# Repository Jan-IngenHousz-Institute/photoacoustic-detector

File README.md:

# photoacoustic-detector

A photoacoustic detector built from a TLV320ADC6120 audio-ADC shield on a
Raspberry Pi Pico (RP2040), an IM73A135 MEMS microphone and an on/off
current source driving a LED. The Pico
switches the LED with a square wave between 200 Hz and 10 kHz, computes the
lock-in amplitude and phase of the microphone signal at that frequency and
streams the raw samples; the PC shows the FFT, the lock-in result and
frequency sweeps.

```
firmware/      Pico SDK (C) firmware, prebuilt image in firmware/release/
pc-gui/        desktop GUI (PySide6) and command-line tools
measurements/  recorded data (first recording 2026-10-30)
kicad/         shield schematic and PCB
doc/           datasheets (ADC, microphone, TI analog-input app note)
legacy/        superseded MicroPython firmware, reference only
```

## Quick start

### 1. What you need

- The assembled detector: Pico with the shield and the microphone on its
  flex, the LED current source wired to the Pico (control input on GP0,
  pin 1; ground on pin 3), a USB cable.
- A PC with Python 3.10 or newer. On Windows use the python.org interpreter
  (`py -3.13`); see the note on Anaconda below.

Safety: the LED current is set in the current-source hardware. Keep it at or
below 1 A, the LED's continuous rating; the Pico only switches it with a
50 % square wave. The firmware holds GP0 low from boot, switches the light
off when no command has arrived from the PC for 5 s, and when the serial
port is closed. Fit a ~100 kOhm pull-down on the control input so the LED
also stays off while the Pico is in reset or in the bootloader.

### 2. Plug the device in

It enumerates as **pa-detector**, a USB serial port (Windows `COMx`, Linux
`/dev/ttyACMx`, macOS `/dev/cu.usbmodem*`). No driver is needed. If a drive
called `RPI-RP2` appears instead, the Pico is in its bootloader: copy
`firmware/release/pa_detector-1.0.1.uf2` onto that drive and it restarts as
the detector (see "Updating the firmware").

### 3. Install and start the GUI

Pick one:

- **Windows, nothing to install (recommended):** download
  `PhotoacousticDetector-windows.zip` from the
  [releases page](https://github.com/Jan-IngenHousz-Institute/photoacoustic-detector/releases),
  unzip it anywhere and double-click `PhotoacousticDetector.exe`. The zip
  also contains the firmware image and this README.
- **Windows, from this repository:** double-click `pc-gui\run_gui.bat`. On
  first use it installs Python 3.13 if the PC has none (python.org build,
  per user, through winget) and creates a private environment in
  `pc-gui\.venv`; later starts take a second. Do not start the GUI from an
  Anaconda prompt: Anaconda's Python cannot load PySide6 (see
  Troubleshooting); the script skips Anaconda on purpose.
- **Linux / macOS:** `sh pc-gui/run_gui.sh` (needs `python3` 3.10 or newer
  with the venv module; on Linux add yourself to the `dialout` group to open
  the serial port).

Manual alternative with any python.org Python 3.10+:
`pip install -r pc-gui/requirements.txt`, then `python pc-gui/pa_gui.py`.
`python pc-gui/pa_gui.py --check` builds the window off-screen and reports
the versions, useful to verify an installation.

**Without the detector:** start the GUI with `--sim`
(`PhotoacousticDetector.exe --sim`, `pc-gui\run_gui.bat --sim` or
`python pc-gui/pa_gui.py --sim`). The port list then offers
`SIM  simulated detector (no hardware)`: a simulated board that speaks the
firmware's protocol and answers like a cell with a resonance at 3 kHz. Use it
to learn the GUI or to try a recorded sweep.

### 4. First measurement

1. Choose the port marked `[pa-detector]` and press **Connect**. The console
   reports `firmware pa-detector 1.0.1` and a status line; the indicators
   for Pico, firmware, ADC, clock and modulator turn green.
2. Press **Self-test...** and **Run device self-test**. Every entry should
   pass; `mic_noise_floor` reads about -80 to -85 dBFS at 12 dB gain in a
   quiet room. **Run light on/off check (2 s)** flashes the LED and reports
   the signal difference at the modulation frequency.
3. In **Excitation (LED current source on GP0)** set the modulation
   frequency (200 Hz to 10 kHz; it snaps to 3.072 MHz / P and the actual
   value is shown next to it). In **ADC (TLV320ADC6120)** set the gain
   (0 to 42 dB); **Auto-range gain** picks it so that the peak sits at
   -12 dBFS.
4. Press **Modulation ON**. The **FFT** tab shows the spectrum of the
   gap-free sample stream with a marker at f_mod and its harmonics, the
   noise floor next to the peak and the SNR; choose 0.1 to 5 s frames and
   the number of averages, **Zoom around f_mod**, **Log frequency**,
   **Export CSV**. The **Lock-in** tab shows amplitude and phase of every
   100 ms block and their running average; **Take dark** with the light
   off stores a dark reference that **Subtract** removes. The **Time
   domain** tab shows the raw block and the synchronous average over one
   modulation period (phase 0 = LED rising edge).
5. The red **LIGHT OFF** button stops the modulation at any time, as does
   closing the GUI or unplugging the USB cable.
6. **Sweep** tab, **Frequency sweep (find cell resonance)**: from/to
   frequency, number of points, log spacing, settle and average blocks,
   **Run sweep**, **Export sweep CSV**. **Record sweep...** asks for a name,
   runs the sweep and saves everything in one file, `<name>.txt`, in the
   data folder (see "Recorded sweeps" below). Switch **Modulation ON**
   first; otherwise the GUI asks whether you mean a dark sweep. At each
   frequency the sweep waits until the board reports the new frequency,
   lets the cell settle for the given number of blocks and then averages.
7. **Data and logging**: the data folder is `photoacoustic-data`, created
   where the GUI is started: next to `PhotoacousticDetector.exe`, or in the
   current folder when run from source (in Documents when that folder is
   read-only). **Open** shows it. **Start logging** writes one CSV row per
   block with the full settings context. **Save config** / **Load config**
   keep the GUI settings.
8. Units: dBFS (sine peak relative to the ADC full scale) or mPa, using the
   **Calibration** fields (microphone -38 dBV/Pa, ADC 2 Vrms full scale at
   0 dB gain).

### 5. Command line instead of the GUI

```
py pc-gui/pa_smoke.py COM9            # self-test, 30 blocks, timing and protocol checks
py pc-gui/pa_smoke.py COM9 --light    # the same plus 2 s of modulation at 1 kHz
py pc-gui/pa_measure.py COM9 --freqs 500,1000,2000,3332 --off 3 --on 5 --cycles 3 --gain 12
```

`pa_measure.py` records, per frequency, light-off and light-on blocks and
writes `results.csv` (lock-in amplitude and phase with the light on, lock-in
level with the light off, FFT peak against the noise floor in 0.2 Hz bins,
odd harmonics, phase spread between light cycles), the spectra, and a
`summary.png` when matplotlib is installed.

## Reading the numbers

- **dBFS**: 0 dBFS is a full-scale sine, 2 Vrms differential at the ADC
  input at 0 dB gain. With the microphone's -38 dBV/Pa, 94 dB SPL reads
  about -44 dBFS at 0 dB gain. The noise floor is about -84 dBFS RMS at
  12 dB gain; the microphone's own noise (21 dB(A) SPL) sets the floor from
  about 20 dB gain upward.
- **Phase**: the lag of the microphone signal behind the LED rising edge,
  as seen at the ADC output. It repeats between light cycles and sessions
  to about a degree. For the physical response subtract the ADC group
  delay, 360 * f_mod * 17.1 / 48000 degrees, and the high-pass filter's
  lead, atan(12 Hz / f_mod).
- **First recording** (`measurements/2026-10-30_led-on-mic/`, the LED
  pointed at the microphone, 12 dB gain): -97 dBFS at 500 Hz falling to
  -112 dBFS at 3.3 kHz, 28 to 35 dB above the noise in 0.2 Hz bins, phase
  repeatable within 0.6 to 2.7 degrees over three light cycles.

## Recorded sweeps

**Record sweep...** saves one tab-separated text file,
`photoacoustic-data/<name>.txt`:

| Part | Content |
|---|---|
| `# key: value` header | the record (start, end, `status: complete` or `aborted: <why>`, counts, the maximum), software, device (port and every field the firmware reports about itself), sweep and measurement settings, calibration, definitions, the device status at the start and at the end, all GUI settings, and the meaning of every column |
| `[analysed]` | one row per frequency: amplitude of the vector average (fraction of full scale, dBFS, dB relative to the sweep's maximum, mPa peak) and its phase, their standard errors, gain, light, overloads |
| `[blocks]` | every 100 ms block that went into the average: the firmware's lock-in values, level and flags, and the lock-in reference phase of its first sample |
| `[samples]` | the raw microphone samples of each of those blocks, 4800 int16 values per row (divide by 32768 for a fraction of full scale) |

The default sweep (50 frequencies x 10 blocks) gives about 7 MB. The blocks
seen while a frequency settles are not in the file. If the window is closed
or the cable pulled during a recorded sweep, what was measured is saved with
an `aborted` status; a block whose raw samples were lost on the USB link is
marked in `[blocks]` and counted in the header.

A spreadsheet opens the tables after you delete the other sections. In
Python:

```
import sys; sys.path.insert(0, "pc-gui")
import pa_record
r = pa_record.read_record("photoacoustic-data/leaf A.txt")
f, amp, ph = r["analysed"]["f_hz"], r["analysed"]["amp_fs"], r["analysed"]["phase_deg"]
x = r["samples"][r["blocks"]["seq"][0]] / 32768      # raw samples of the first block
```

## Updating the firmware

The tested image is `firmware/release/pa_detector-1.0.1.uf2` (also inside
the standalone zip).

1. Get the Pico into its bootloader: with the GUI connected press
   **Update firmware...** in the Tools group (it sends the `bootsel` command
   and disconnects), or hold the BOOTSEL button on the Pico while plugging
   the USB cable in.
2. Copy the UF2 onto the `RPI-RP2` drive that appears (the GUI's status bar
   points it out). The Pico restarts as pa-detector within a few seconds;
   the port number may change, press **Refresh** and connect again.

Building from source, the serial protocol, the clock scheme and the safety
design are documented in `firmware/README.md`.

## Troubleshooting

| Symptom | What to do |
|---|---|
| No serial port, no `RPI-RP2` drive | Try another cable or USB port (data cable, not charge-only). |
| `RPI-RP2` drive, no port | The Pico has no firmware: copy the UF2 from `firmware/release/` onto the drive. |
| Port is shown as `[Pico, MicroPython: old firmware]` | The board still runs the legacy firmware: `mpremote exec "import machine; machine.bootloader()"`, then copy the UF2. |
| "no firmware answer" after Connect | Another program holds the port (close it), or the board is not running the detector firmware. |
| `DLL load failed while importing QtCore` | The GUI was started with Anaconda's Python, whose MSVC runtime is too old for PySide6. Use `run_gui.bat` or the standalone build. Inside conda it works from a dedicated environment: `conda create -n pa -c conda-forge python=3.12 pyside6 pyqtgraph pyserial numpy`, then `conda activate pa`. |
| `adc_*` self-test entries fail | ADC or I2C problem on the shield; `dump` prints the registers. |
| `mic_noise_floor` fails as silent | Microphone unpowered or flex not seated; check MICBIAS (2.75 V) at the connector. |
| Full-scale noise on the microphone channel | The ADC's AREG regulator is oscillating: C5 must be 10 uF (see Hardware notes). |
| Light never comes on | Check the GP0 wiring and the current source; the firmware switches the light off 5 s after the last command, so keep the GUI (or a `ping` every second) running. |

## Measurement principle

The Pico generates the I2S clocks itself from a 76.8 MHz system clock with
integer dividers, so the ADC samples at exactly 48000.000 Hz. A PIO state
machine counts I2S bit clocks (64 per sample), so the modulation period is a
whole number P of bit clocks and f_mod = 3.072 MHz / P exactly (P = 308 to
15360). The modulator is started on a known sample frame and the lock-in
reference on the Pico runs at the same ratio with phase 0 on the LED rising
edge, so the reference never drifts against the light, successive 100 ms
blocks average coherently, and the phase is reproducible. Each block gives
the amplitude and phase of the photoacoustic response, which the PC
averages, plots and logs; the raw samples of every block go to the PC for
the FFT. The lock-in uses the ADC's 24-bit samples; the streamed samples are
16-bit.

## Hardware notes

| Function                   | Pico pin        | Notes                                                        |
|----------------------------|-----------------|--------------------------------------------------------------|
| ADC I2C SDA / SCL          | GP4 / GP5       | on the shield, 2k2 pull-ups to 3V3                           |
| ADC BCLK / FSYNC / SDOUT   | GP6 / GP7 / GP8 | Pico is I2S master: 3.072 MHz, 48 kHz, 24-bit in 32-bit slots |
| ADC GPIO1 ("EXT")          | GP9             | unused (ADC interrupt output)                                 |
| LED current source control | GP0 (pin 1)     | 3.3 V = LED on, 0 V = off; fit a ~100 kOhm pull-down          |
| GND                        | GND (pin 3)     | common ground with the current source                        |

The ADC's internal AREG regulator needs 10 uF + 100 nF (datasheet). The
first PCB has C5 = 1 uF, which made AREG oscillate (2.1 V average, full-scale
noise on the microphone channel); fit a 10 uF 6.3 V X5R there. The KiCad
project in `kicad/` still shows 1 uF.

## Making a release (maintainers)

Before a release, run the GUI test, which needs no hardware: it drives the
real GUI off-screen against the simulated detector, records sweeps and checks
the files (exit code 0 = pass, about 10 s):

```
pc-gui\.venv\Scripts\python.exe pc-gui\test_record.py
```

The GUI version is `GUI_VERSION` in `pc-gui/pa_gui.py`, the firmware version
`FW_VERSION` in `firmware/src/board.h`. `pc-gui\build_exe.bat` builds the
standalone Windows GUI with PyInstaller into
`pc-gui\dist\PhotoacousticDetector\` and zips it as
`pc-gui\dist\PhotoacousticDetector-windows.zip` (firmware image and README
included). Publish it together with the firmware image:

```
gh release create v1.1.0 pc-gui/dist/PhotoacousticDetector-windows.zip firmware/release/pa_detector-1.0.1.uf2
```

## Legacy

`legacy/firmware-micropython/` is the first, MicroPython firmware. It is no
longer used by the GUI or the tools; see `legacy/README.md`.

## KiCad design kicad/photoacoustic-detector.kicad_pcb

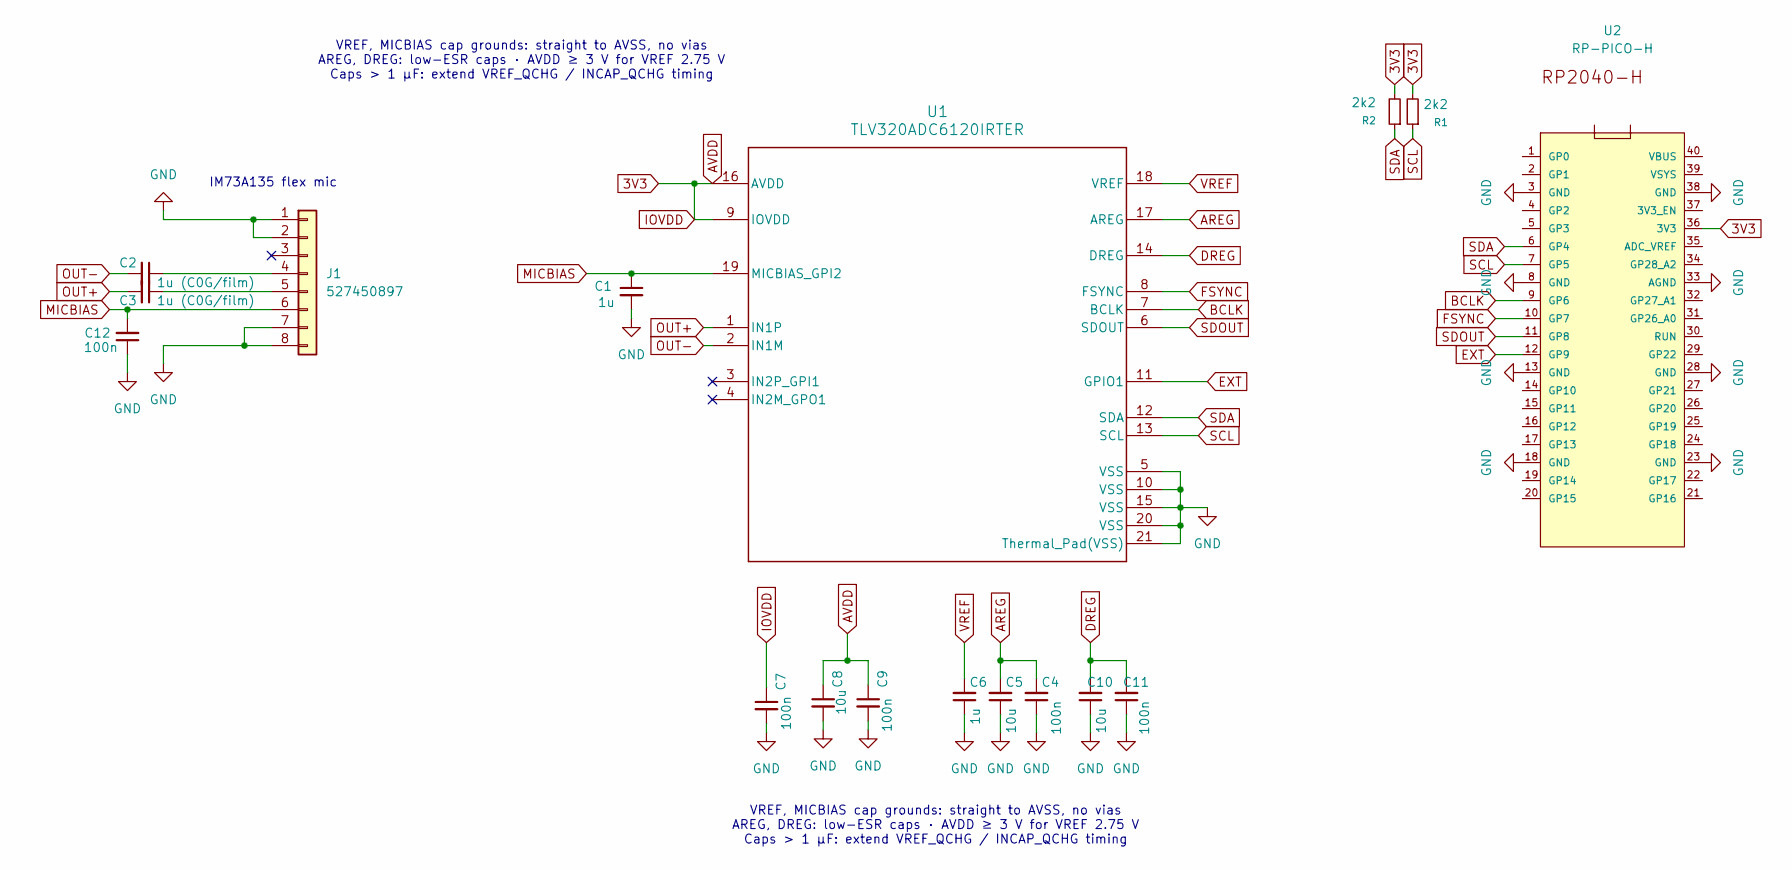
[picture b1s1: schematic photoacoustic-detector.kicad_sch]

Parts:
C1, C6: 1u; C_0201_0603Metric_Pad0.64x0.40mm_HandSolder
C2, C3: 1u (C0G/film); C_0201_0603Metric_Pad0.64x0.40mm_HandSolder
C4, C7, C9, C11, C12: 100n; C_0201_0603Metric_Pad0.64x0.40mm_HandSolder
C5, C8, C10: 10u; C_0201_0603Metric_Pad0.64x0.40mm_HandSolder
J1: 527450897; CONN_527450897_MOL
R1, R2: 2k2; R_0201_0603Metric_Pad0.64x0.40mm_HandSolder
U1: TLV320ADC6120IRTER; TLV320ADC6120
U2: RP-PICO-H; RP2040-PICO

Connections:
3V3: C7.1, C8.1, C9.1, R1.2, R2.2, U1.9 (IOVDD), U1.16 (AVDD), U2.36 (3V3)
AREG: C4.2, C5.2, U1.17 (AREG)
BCLK: U1.7 (BCLK), U2.9 (GP6)
DREG: C10.2, C11.2, U1.14 (DREG)
EXT: U1.11 (GPIO1), U2.12 (GP9)
FSYNC: U1.8 (FSYNC), U2.10 (GP7)
GND: C1.2, C4.1, C5.1, C6.1, C7.2, C8.2, C9.2, C10.1, C11.1, C12.1, J1.1, J1.2, J1.7, J1.8, U1.5 (VSS), U1.10 (VSS), U1.15 (VSS), U1.20 (VSS), U1.21 (Thermal_Pad(VSS)), U2.3 (GND), U2.8 (GND), U2.13 (GND), U2.18 (GND), U2.23 (GND), U2.28 (GND), U2.33 (AGND), U2.38 (GND)
MICBIAS: C1.1, C12.2, J1.6, U1.19 (MICBIAS_GPI2)
unnamed: C2.1, J1.4
unnamed: C3.1, J1.5
OUT+: C3.2, U1.1 (IN1P)
OUT-: C2.2, U1.2 (IN1M)
SCL: R1.1, U1.13 (SCL), U2.7 (GP5)
SDA: R2.1, U1.12 (SDA), U2.6 (GP4)
SDOUT: U1.6 (SDOUT), U2.11 (GP8)
VREF: C6.2, U1.18 (VREF)

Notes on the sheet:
IM73A135 flex mic
VREF, MICBIAS cap grounds: straight to AVSS, no vias AREG, DREG: low-ESR caps · AVDD ≥ 3 V for VREF 2.75 V Caps > 1 µF: extend VREF_QCHG / INCAP_QCHG timing

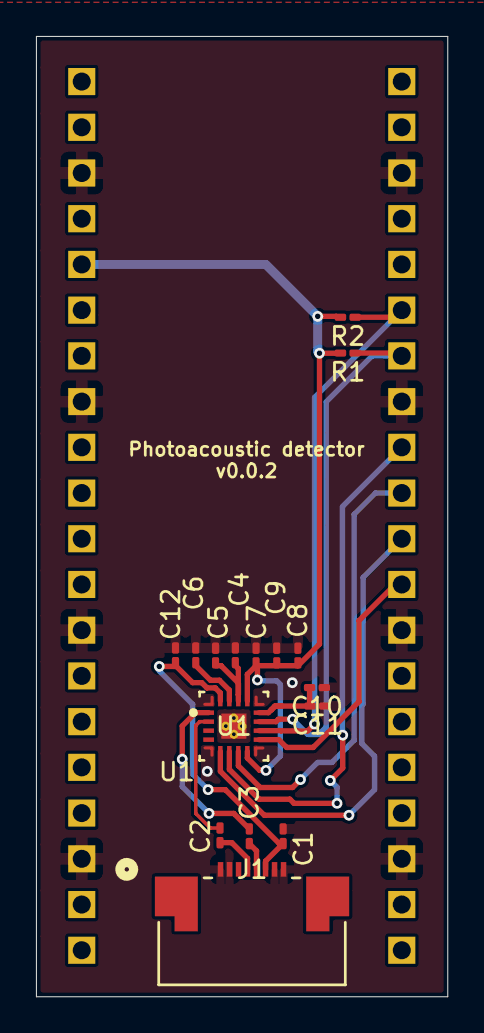
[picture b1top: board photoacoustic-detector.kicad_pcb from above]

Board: 2 copper layers, 22.8 x 53.4 mm, 17 parts (1 on the bottom side), 16 nets.

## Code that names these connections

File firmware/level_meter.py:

"""
level_meter.py - stand-alone bring-up test for the shield (no PC software).

1. Checks that the TLV320ADC6120 answers on I2C (GP4 = SDA, GP5 = SCL).
2. Brings the ADC up: I2S slave, channel 1 differential mic input, 48 kHz.
3. Starts the Pico I2S master on GP6 (BCLK), GP7 (FSYNC), GP8 (SDOUT).
4. Prints the ADC clock/mode status and a running signal level of channel 1.

Run it from the REPL with:  import level_meter
The onboard LED blinks fast if the ADC is missing, slow while running.
"""

from machine import I2C, I2S, Pin
from array import array
import math
import time

import TLV320

PIN_SDA = 4
PIN_SCL = 5
PIN_BCLK = 6      # I2S sck  (ws must be sck + 1 on the RP2040 port)
PIN_FSYNC = 7     # I2S ws
PIN_SDOUT = 8     # I2S sd (input)
PIN_LED = 25      # Pico H onboard LED

SAMPLE_RATE = 48_000
BITS = 32                 # 32-bit stereo -> BCLK/FSYNC ratio 64, supported by the ADC
GAIN_DB = 12              # analog gain, 0..42 dB
FRAMES = 2048             # frames per read (stereo -> 2 samples per frame)

led = Pin(PIN_LED, Pin.OUT)


def blink_forever(period_ms):
    while True:
        led.toggle()
        time.sleep_ms(period_ms)


def level_dbfs(buf, step=2, offset=0):
    """RMS and peak of every `step`-th sample, in dBFS (32-bit full scale)."""
    fs = 2147483647.0
    acc = 0.0
    peak = 0
    n = 0
    for i in range(offset, len(buf), step):
        v = buf[i]
        acc += float(v) * v
        a = -v if v < 0 else v
        if a > peak:
            peak = a
        n += 1
    rms = math.sqrt(acc / n) if n else 0.0
    to_db = lambda x: 20 * math.log10(x / fs) if x > 0 else -200.0
    return to_db(rms), to_db(peak)


i2c = I2C(0, sda=Pin(PIN_SDA), scl=Pin(PIN_SCL), freq=400_000)
print("I2C devices:", [hex(a) for a in i2c.scan()])

adc = TLV320.TLV320ADC6120(i2c)
if not adc.detect():
    print("TLV320ADC6120 NOT found at 0x%02X" % TLV320.I2C_ADDR)
    blink_forever(100)
print("TLV320ADC6120 found at 0x%02X" % TLV320.I2C_ADDR)

adc.reset()
mismatch = adc.verify()
if mismatch:
    print("warning: unexpected reset values (reg, got, expected):", mismatch)
else:
    print("register defaults match TLV320ADC6120 datasheet")

adc.begin(bits=BITS, gain_db=GAIN_DB)

i2s = I2S(0, sck=Pin(PIN_BCLK), ws=Pin(PIN_FSYNC), sd=Pin(PIN_SDOUT),
          mode=I2S.RX, bits=BITS, format=I2S.STEREO, rate=SAMPLE_RATE,
          ibuf=FRAMES * 2 * (BITS // 8) * 4)

time.sleep_ms(50)
st = adc.status()
print("ADC status:", st)
if not st["clock_ok"]:
    print("warning: ADC did not detect a valid FSYNC/BCLK ratio")

buf = array("i", (0 for _ in range(FRAMES * 2)))
mv = memoryview(buf)

print("streaming channel 1 (left slot)... Ctrl-C to stop")
try:
    t_last = time.ticks_ms()
    while True:
        n = i2s.readinto(mv)
        if n == 0:
            continue
        rms, peak = level_dbfs(buf, step=2, offset=0)
        if time.ticks_diff(time.ticks_ms(), t_last) >= 500:
            t_last = time.ticks_ms()
            led.toggle()
            print("CH1  rms %6.1f dBFS   peak %6.1f dBFS" % (rms, peak))
except KeyboardInterrupt:
    pass
finally:
    i2s.deinit()
    adc.power_down()
    adc.sleep()
    led.off()
    print("stopped, ADC in sleep mode")
